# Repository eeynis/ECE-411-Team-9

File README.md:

# ECE-411-Team-9
The current Github repository contains our up-to-date code, as well as a link to a google drive which contains all our project files.

https://drive.google.com/drive/folders/1lPI17c37aat8llfF2yd1i48d-kb0khAg?usp=sharing

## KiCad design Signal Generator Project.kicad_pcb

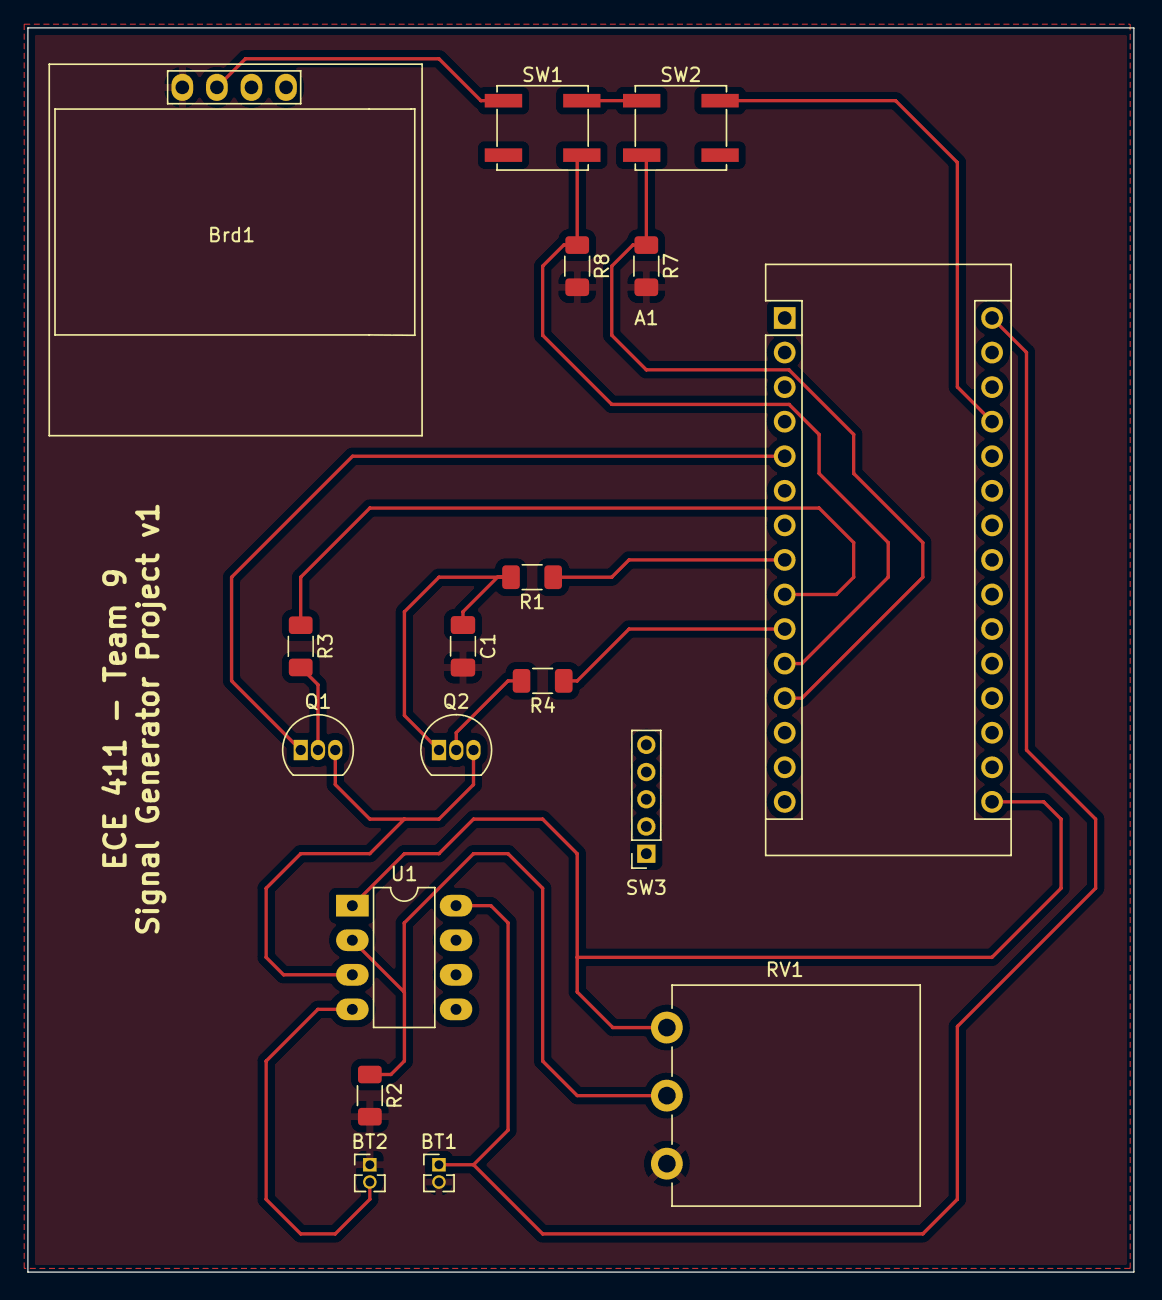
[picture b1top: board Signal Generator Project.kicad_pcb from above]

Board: 2 copper layers, 81.3 x 91.4 mm, 18 parts (0 on the bottom side), 18 nets.

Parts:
A1: Arduino_Nano_v3.x; Arduino_Nano
BT1, BT2: 9V; PinHeader_1x02_P1.27mm_Vertical
Brd1: SSD1306; 128x64OLED
C1: 0.1uF; C_1206_3216Metric_Pad1.33x1.80mm_HandSolder
Q1, Q2: BS170; TO-92_Inline
R1: 5.6k; R_1206_3216Metric_Pad1.30x1.75mm_HandSolder
R2, R7, R8: 10k; R_1206_3216Metric_Pad1.30x1.75mm_HandSolder
R3, R4: 100; R_1206_3216Metric_Pad1.30x1.75mm_HandSolder
RV1: 100k; Potentiometer_Piher_PC-16_Single_Vertical
SW1, SW2: SW_Push; SW_SPST_EVQP0
SW3: KY-040; PinSocket_1x05_P2.00mm_Vertical
U1: LM358; DIP-8_W7.62mm_LongPads

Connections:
GND: BT1.2 (-), BT2.1 (+), Brd1.1 (GND), C1.2, R2.2, R7.2, R8.2, RV1.1
unnamed: A1.5 (D2), Q1.1 (D)
unnamed: A1.6 (D3), Brd1.3 (SCL)
unnamed: A1.7 (D4), Brd1.4 (SDA)
unnamed: A1.8 (D5), R1.1
unnamed: A1.9 (D6), R3.1
unnamed: A1.10 (D7), R4.1
unnamed: A1.11 (D8), R8.1, SW1.2
unnamed: A1.12 (D9), R7.1, SW2.2
unnamed: A1.27 (+5V), Brd1.2 (VCC), SW1.1, SW2.1
unnamed: A1.30 (VIN), BT1.1 (+), U1.8 (V+)
unnamed: BT2.2 (-), U1.4 (V-)
unnamed: C1.1, Q2.1 (D), R1.2
unnamed: Q1.2 (G), R3.2
unnamed: Q1.3 (S), Q2.3 (S), U1.3 (+)
unnamed: Q2.2 (G), R4.2
unnamed: R2.1, RV1.2, U1.2 (-)
V_out: A1.16 (D13), RV1.3, U1.1

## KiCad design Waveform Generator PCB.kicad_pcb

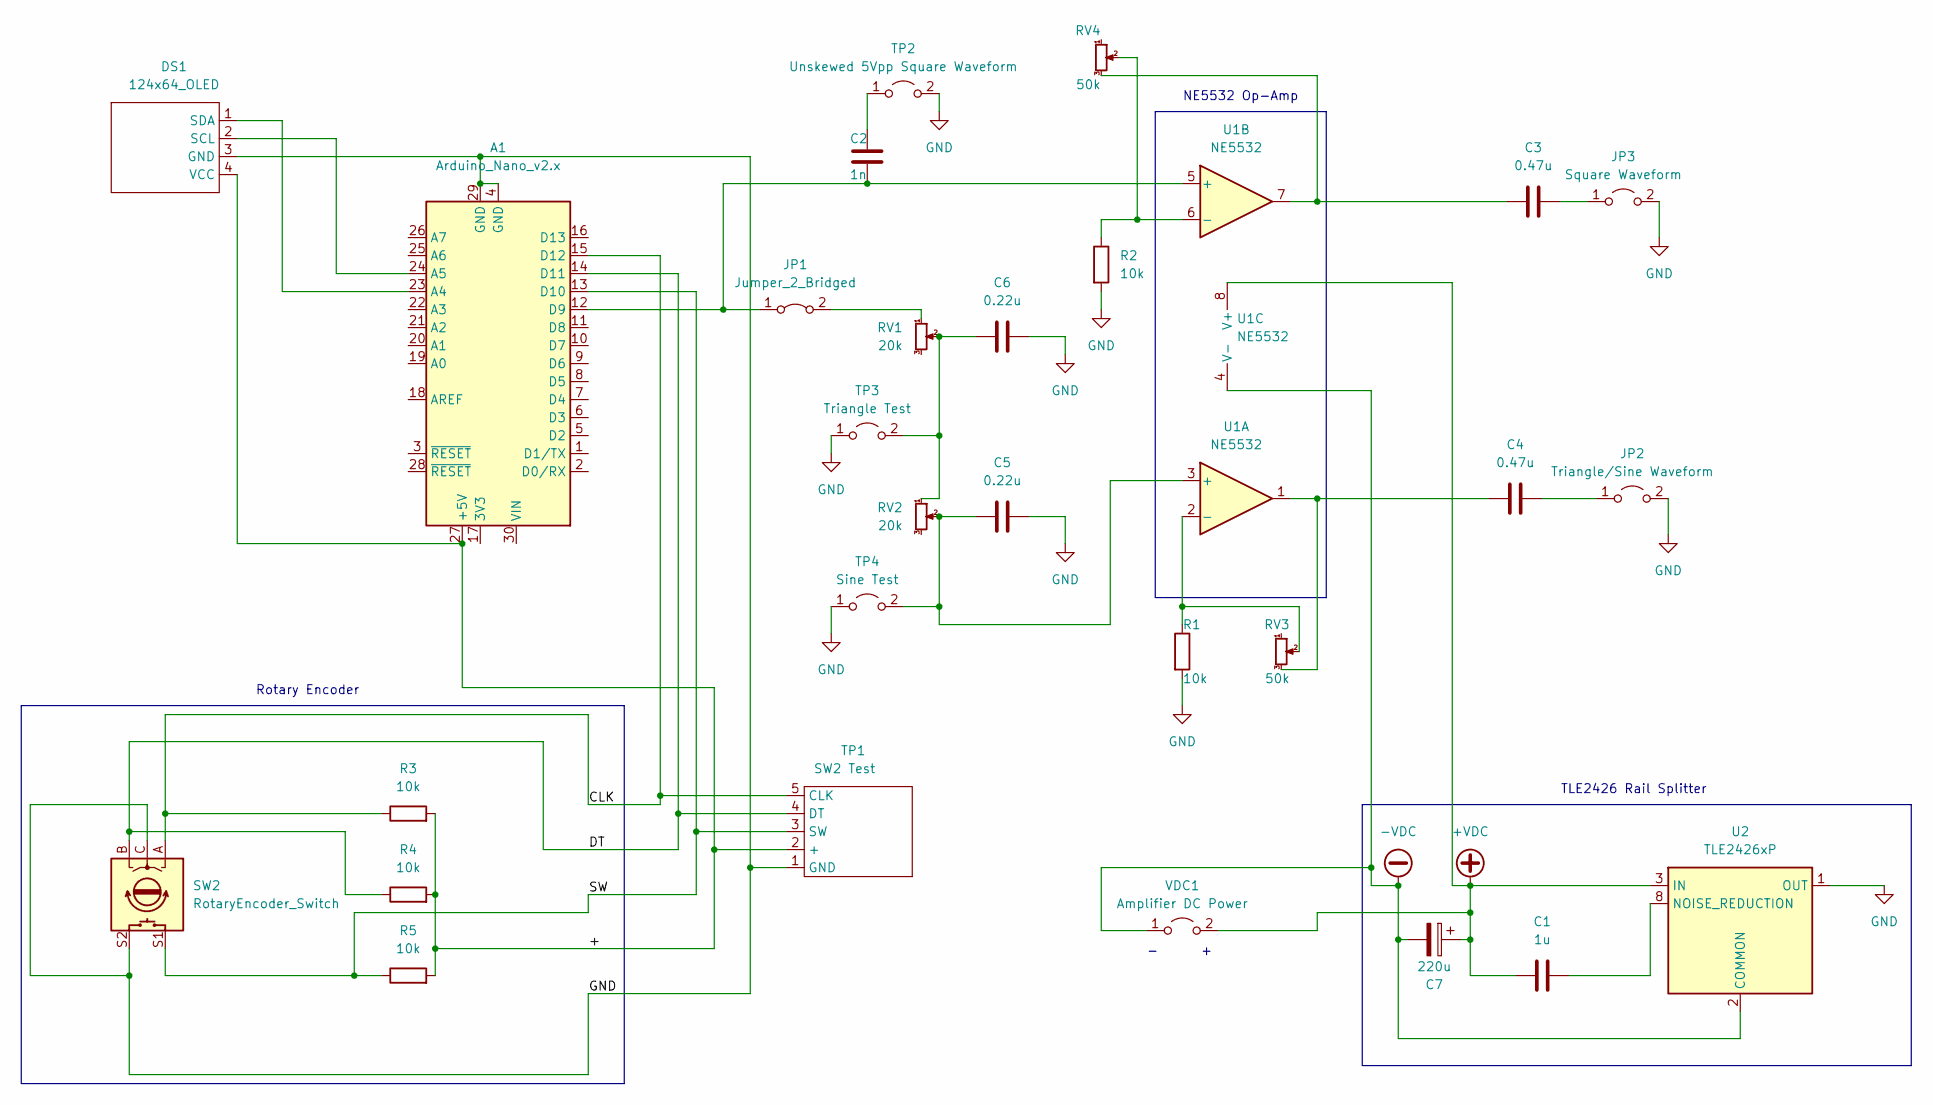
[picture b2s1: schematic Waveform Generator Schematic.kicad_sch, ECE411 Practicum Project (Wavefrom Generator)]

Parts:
A1: Arduino_Nano_v2.x; Arduino_Nano
C1: 1u; C_1206_3216Metric_Pad1.33x1.80mm_HandSolder
C2: 1n; C_1206_3216Metric_Pad1.33x1.80mm_HandSolder
C3, C4: 0.47u; C_1206_3216Metric_Pad1.33x1.80mm_HandSolder
C5, C6: 0.22u; C_1206_3216Metric_Pad1.33x1.80mm_HandSolder
C7: 220u; CP_Radial_D10.0mm_P5.00mm
DS1: 124x64_OLED; PinHeader_1x04_P2.54mm_Vertical
JP1: Jumper_2_Bridged; PinHeader_1x02_P2.54mm_Vertical
JP2: Triangle/Sine Waveform; TestPoint_2Pads_Pitch2.54mm_Drill0.8mm
JP3: Square Waveform; TestPoint_2Pads_Pitch2.54mm_Drill0.8mm
R1, R2, R3, R4, R5: 10k; R_1206_3216Metric_Pad1.30x1.75mm_HandSolder
RV1, RV2: 20k; Potentiometer_Bourns_PTV09A-1_Single_Vertical
RV3, RV4: 50k; Potentiometer_Bourns_PTV09A-1_Single_Vertical
SW2: RotaryEncoder_Switch; RotaryEncoder_Alps_EC11E-Switch_Vertical_H20mm
TP1: SW2 Test; PinHeader_1x05_P2.54mm_Vertical
TP2: Unskewed 5Vpp Square Waveform; TestPoint_2Pads_Pitch2.54mm_Drill0.8mm
TP3: Triangle Test; TestPoint_2Pads_Pitch2.54mm_Drill0.8mm
TP4: Sine Test; TestPoint_2Pads_Pitch2.54mm_Drill0.8mm
U1: NE5532; DIP-8_W7.62mm_LongPads
U2: TLE2426xP; DIP-8_W7.62mm
VDC1: Amplifier DC Power; TestPoint_2Pads_Pitch2.54mm_Drill0.8mm

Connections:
+VDC: C1.1, C7.1, U1.8 (V+), U2.3 (IN), VDC1.2 (B)
-VDC: C7.2, U1.4 (V-), U2.2 (COMMON), VDC1.1 (A)
/+: A1.27 (+5V), DS1.4 (VCC), R3.2, R4.2, R5.2, TP1.2 (+)
/CLK: A1.15 (D12), R3.1, SW2.A, TP1.5 (CLK)
/DT: A1.14 (D11), R4.1, SW2.B, TP1.4 (DT)
/SW: A1.13 (D10), R5.1, SW2.S1, TP1.3 (SW)
GND: A1.4 (GND), A1.29 (GND), C5.2, C6.2, DS1.3 (GND), JP2.2 (B), JP3.2 (B), R1.2, R2.2, SW2.C, SW2.S2, TP1.1 (GND), TP2.2 (B), TP3.1 (A), TP4.1 (A), U2.1 (OUT)
unnamed: C3.2, JP3.1 (A)
unnamed: C4.2, JP2.1 (A)
unnamed: A1.23 (A4), DS1.1 (SDA)
unnamed: A1.24 (A5), DS1.2 (SCL)
unnamed: JP1.2 (B), RV1.1
unnamed: C6.1, RV1.2, RV2.1, TP3.2 (B)
unnamed: C3.1, RV4.3, U1.7
unnamed: C2.2, TP2.1 (A)
unnamed: C4.1, RV3.3, U1.1
unnamed: R1.1, RV3.2, U1.2 (-)
unnamed: C5.1, RV2.2, TP4.2 (B), U1.3 (+)
unnamed: A1.12 (D9), C2.1, JP1.1 (A), U1.5 (+)
unnamed: R2.1, RV4.2, U1.6 (-)
unnamed: C1.2, U2.8 (NOISE_REDUCTION)

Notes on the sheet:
Rotary Encoder
NE5532 Op-Amp
TLE2426 Rail Splitter

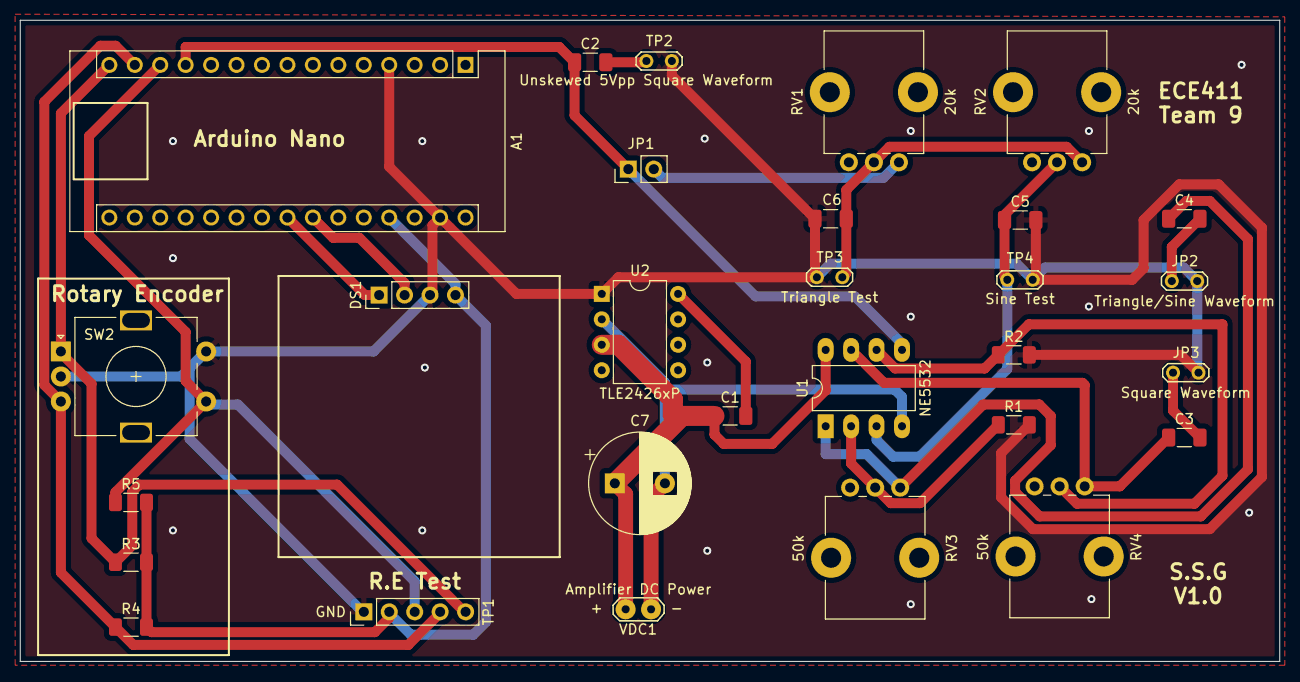
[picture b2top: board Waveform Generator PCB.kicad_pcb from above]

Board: 2 copper layers, 125.7 x 64.0 mm, 29 parts (0 on the bottom side), 21 nets.

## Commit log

2021-10-28 Create Preliminary Breadboard Circuit
2021-10-28 Current Arduino Code (10/27/2021)
    The current code is set to output a 10kHz 50% Duty Cycle square pulse waveform. The commented out code is preliminary code for the OLED display which doesn't behave at the moment.
    The goal is to control the frequency modulation via a rotary encoder and display it on the screen as well as the selected waveform.
2021-11-04 Add files via upload
    These files are for signal generator version 2.0.
2021-11-16 Add files via upload
    These are the latest versions of our schematic and PCB layout.
2021-12-09 Update Current Arduino Code
